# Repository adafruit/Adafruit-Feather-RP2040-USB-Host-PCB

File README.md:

## Adafruit Feather RP2040 with USB Host PCB

<a href="http://www.adafruit.com/products/5723"><br/>
Click here to purchase one from the Adafruit shop</a>

PCB files for the Adafruit Feather RP2040 with USB Host. 

Format is EagleCAD schematic and board layout
* https://www.adafruit.com/product/5723

### Description

You're probably really used to microcontroller boards with USB, but what about a dev board with two? Two is more than one, so that makes it twice as good! And the Adafruit Feather RP2040 with USB Host is definitely double-the-fun of our other Feather RP2040 boards, with a USB Type A port on the end for connecting USB devices to. 

Now you might be thinking "hey waitaminute, the RP2040 doesn't have two USB port peripherals???" and you'd be correct! But what it does have is a nifty PIO peripheral that can be (ab)used to emulate a USB host peripheral. You get to keep the main USB port for uploading, debugging, and data communication, while at the same time sending and receiving data to just-about-any USB device. [This work is originally by sekigon on GitHub](https://github.com/sekigon-gonnoc/Pico-PIO-USB), and if you're using Pico SDK that's still the recommended library to use.

Currently, support for the USB Host peripheral is only in Arduino. So check out the [TinyUSB 'dual role' examples](https://github.com/adafruit/Adafruit_TinyUSB_Arduino/tree/master/examples/DualRole) for some things you can do! For example, [datalogging to a USB Key](https://github.com/adafruit/Adafruit_TinyUSB_Arduino/tree/master/examples/DualRole/MassStorage/msc_data_logger). Or [reading from another device/microcontroller that has USB CDC serial interface](https://github.com/adafruit/Adafruit_TinyUSB_Arduino/tree/master/examples/DualRole/CDC/serial_host_bridge). Or [creating an HID re-mapper](https://github.com/adafruit/Adafruit_TinyUSB_Arduino/tree/master/examples/DualRole/HID/hid_remapper). Or [connecting to weird devices that require firmware-updates like the Cypress EZ-USB based Intellikeys](https://github.com/adafruit/Adafruit_IntelliKeys) communications board.

Note that this is definitely a firmware hack: you will need to dedicate the second ARM core and both PIO peripherals to just handling the USB messages, but we find that it does work fairly well, or at least as well as most microcontroller's USB Host peripherals!

We also include a 1 Amp boost converter based on the TPS61023 so you can run from Lipo battery and get a nice clean 5V output for the USB devices. The booster has the enable pin tied to one of the extra GPIO on the RP2040 so power can be manually turned on and off to hard-reset whatever is connected.

At the Feather's heart is an RP2040 chip, clocked at 133 MHz and at 3.3V logic, the same one used in the Raspberry Pi Pico. This chip has a whopping 8MB of onboard QSPI FLASH and 264K of RAM!  There's even room left over for a STEMMA QT connector for plug-and-play of I2C devices!

To make it easy to use for portable projects, we added a connector for any of our 3.7V Lithium polymer batteries and built-in battery charging. You don't need a battery, it will run just fine straight from the USB Type C connector. But, if you do have a battery, you can take it on the go, then plug in the USB to recharge. The Feather will automatically switch over to USB power when it's available.

Here're some handy specs! You get:

* Measures 2.0" x 0.9" x 0.28" (50.8mm x 22.8mm x 7mm) without headers soldered in
* Light as a (large?) feather - 6.3 grams
* RP2040 32-bit Cortex M0+ dual core running at ~133 MHz @ 3.3V logic and power
* 264 KB RAM
* 8 MB SPI FLASH chip for storing files and CircuitPython/MicroPython code storage. No EEPROM
* Tons of GPIO! 21 x GPIO pins with following capabilities:
* Four 12-bit ADCs (one more than Pico)
* Two I2C, Two SPI, and two UART peripherals, we label one for the 'main' interface in standard Feather locations
* 16 x PWM outputs - for servos, LEDs, etc
* Built-in 200mA+ lipoly charger with charging status indicator LED
* Pin #13 red LED for general purpose blinking
* RGB NeoPixel for full-color indication.
* On-board STEMMA QT connector that lets you quickly connect any Qwiic, STEMMA QT or Grove I2C devices with no soldering!
* Both Reset button and Bootloader select button for quick restarts (no unplugging-replugging to relaunch code)
* USB Type C connector lets you access built-in ROM USB bootloader and serial port debugging
* USB Type A connector for USB host capability. D+ on GPIO 16, D- on GPIO 17
* 5V Boost converter, up to 1 Amp peak output for USB peripheral power, with 500mA resettable fuse. Enable on GPIO 18. 
* 3.3V Power/enable pin
* 4 mounting holes
* 12 MHz crystal for perfect timing.
* 3.3V regulator with 500mA peak current output

### License

Adafruit invests time and resources providing this open source design, please support Adafruit and open-source hardware by purchasing products from [Adafruit](https://www.adafruit.com)!

Designed by Limor Fried/Ladyada for Adafruit Industries.

Creative Commons Attribution/Share-Alike, all text above must be included in any redistribution. 
See license.txt for additional details.

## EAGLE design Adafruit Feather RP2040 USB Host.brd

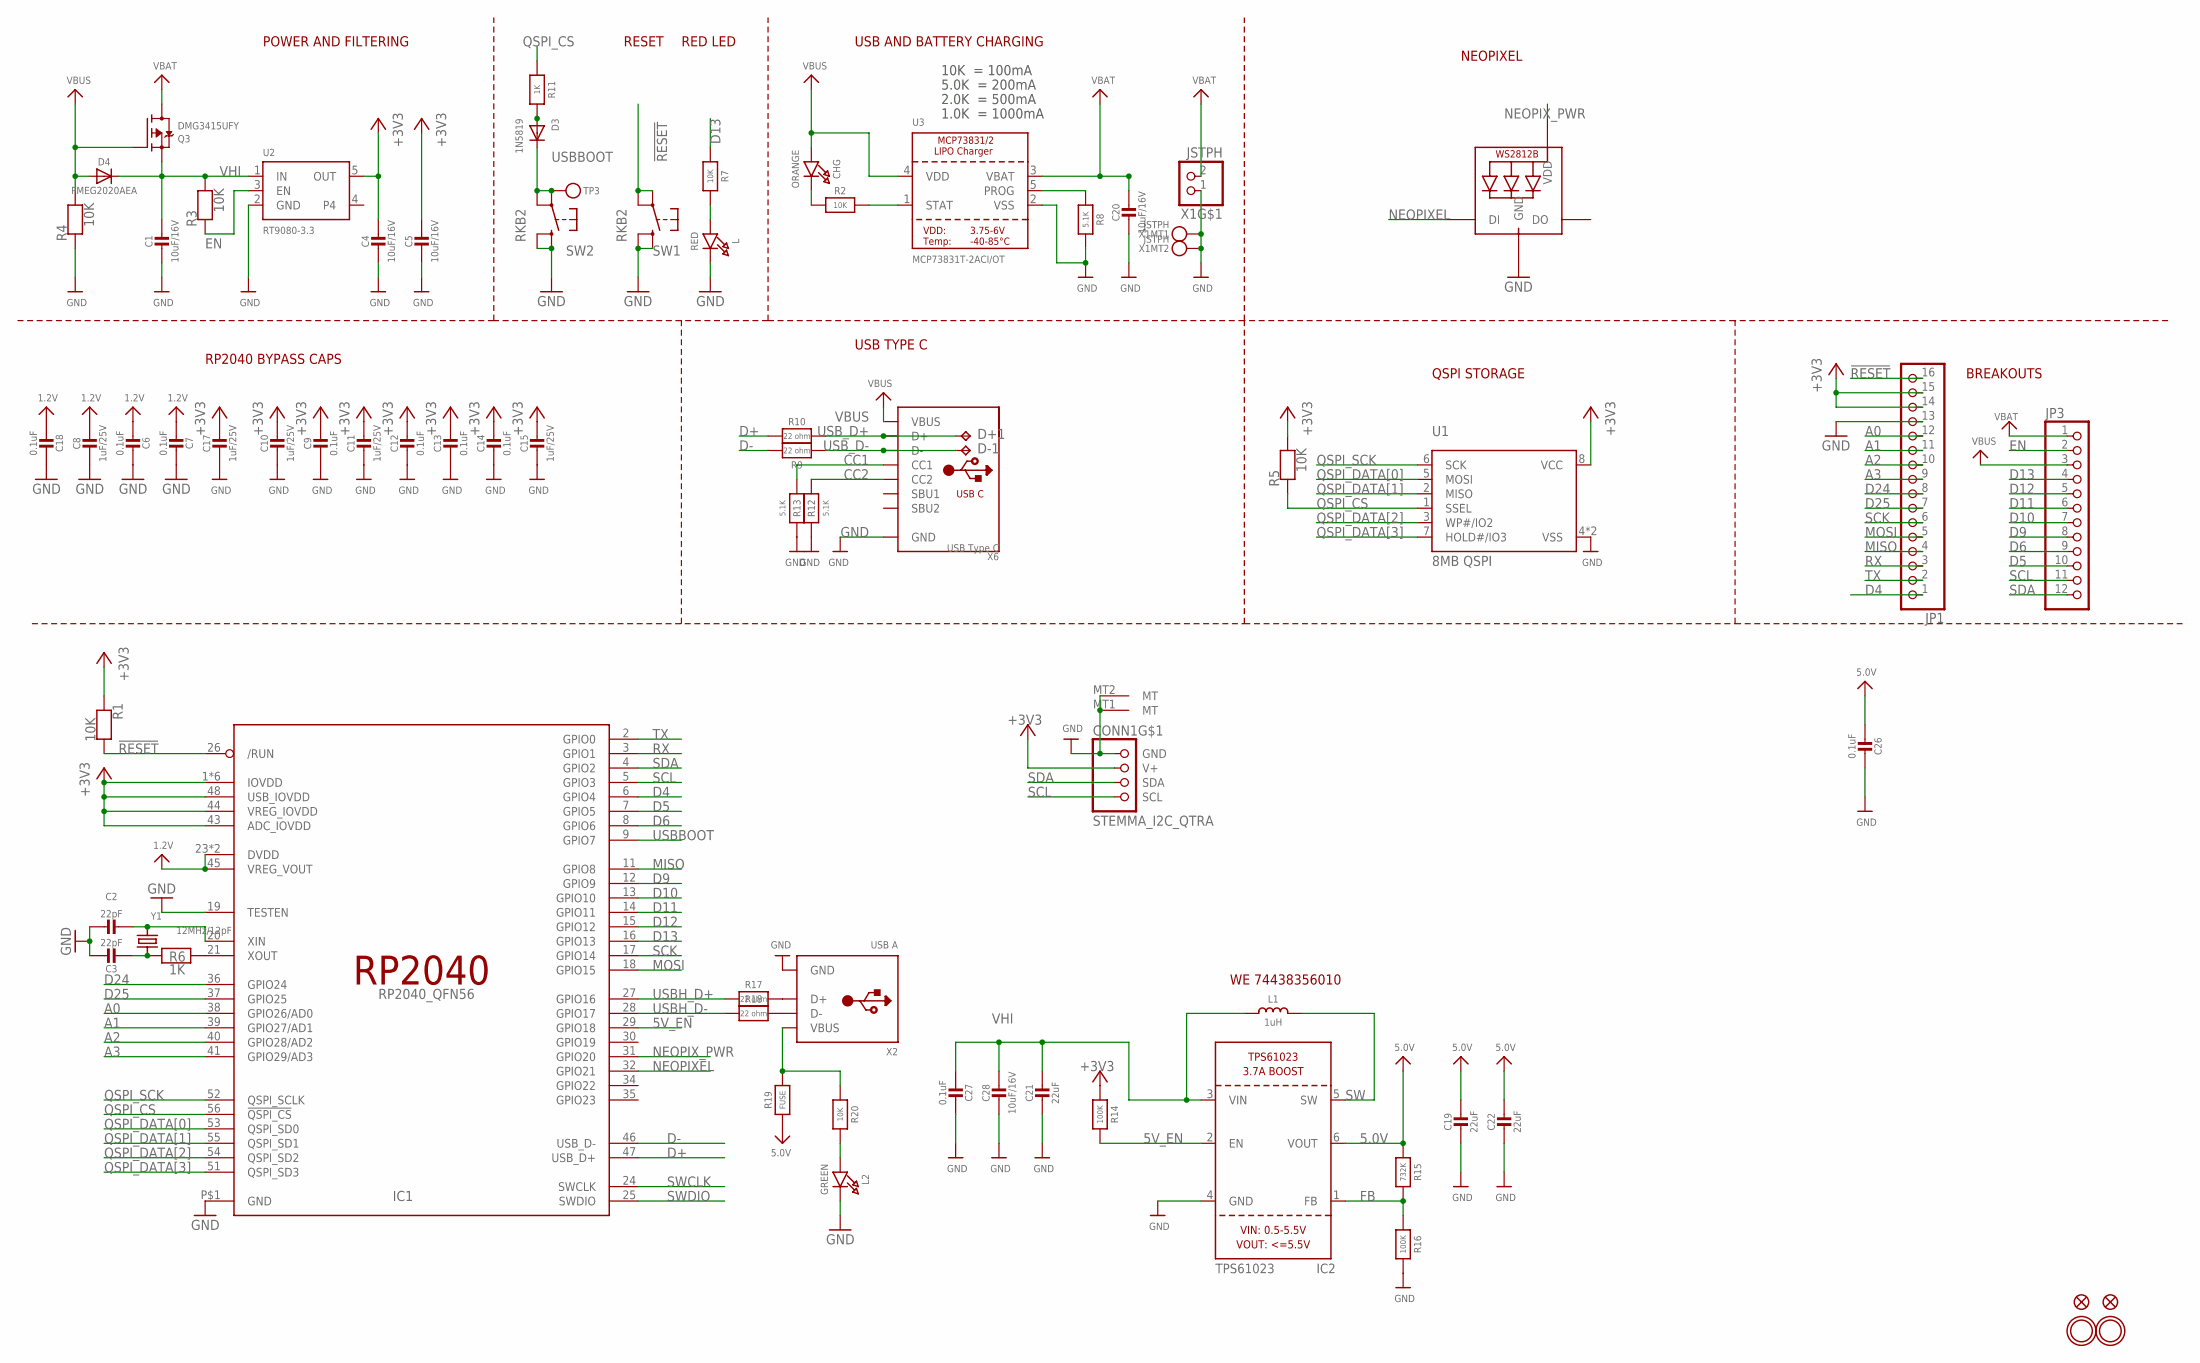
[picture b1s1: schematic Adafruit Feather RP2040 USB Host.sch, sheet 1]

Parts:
C1, C4, C5, C20, C28: 10uF/16V; 0805-NO
C2, C3: 22pF; _0402NO
C6, C7, C9, C12, C13, C14, C18, C26, C27: 0.1uF; _0402NO
C8, C10, C11, C15, C17: 1uF/25V; _0402NO
C19, C21, C22: 22uF; 0805-NO
CHG: ORANGE; CHIPLED_0603_NOOUTLINE
CONN1: STEMMA_I2C_QTRA; JST_SH4_RA
D3: 1N5819; SOD-323_MINI
D4: PMEG2020AEA; SOD-323F
D+1: TPB1,27; B1,27
D-1: TPB1,27; B1,27
IC1: RP2040_QFN56; QFN56_7MM_REDUCEDEPAD
IC2: TPS61023; SOT563
JP1: HEADER-1X16ROUND; 1X16_ROUND
JP3: HEADER-1X12; 1X12_ROUND
L: RED; CHIPLED_0603_NOOUTLINE
L1: 1uH; INDUCTOR_5045_SMALLTABS
L2: GREEN; CHIPLED_0603_NOOUTLINE
LED1: WS2812B_SK6805_1515; SK6805_1515
Q3: DMG3415UFY; DFN2015-3
R1, R2, R3, R4, R5, R7, R20: 10K; _0402NO
R6, R11: 1K; _0402NO
R8, R12, R13: 5.1K; _0402NO
R9, R10, R17, R18: 22 ohm; _0402NO
R14, R16: 100K; _0402NO
R15: 732K; _0402NO
R19: FUSE; 0805-NO
SW1, SW2: RKB2; BTN_RKB2_4.6X2.8
TP3: TESTPOINTROUND1.5MMNO; TESTPOINT_ROUND_1.5MM_NO
U1: 8MB QSPI; USON8_4X4
U2: RT9080-3.3; SOT23-5; JLC_ROTATION 0
U3: MCP73831T-2ACI/OT; SOT23-5
U$31, U$32: MOUNTINGHOLE2.5; MOUNTINGHOLE_2.5_PLATED
U$34, U$35: FIDUCIAL_1MM
X1: JSTPH; JSTPH2_BATT
X2: USB A; USB_HOST-SMT
X6: USB Type C; USB_C_CUSB31-CFM2AX-01-X
Y1: 12MHz/12pF; CRYSTAL_2.5X2

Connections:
1.2V: C6.2, C7.2, C8.1, C18.2, IC1.23 (DVDD), IC1.45 (VREG_VOUT), IC1.50 (DVDD)
5.0V: C19.1, C22.1, C26.2, IC2.6 (VOUT), R15.1, R19.2
5V_EN: IC1.29 (GPIO18), IC2.2 (EN), R14.2
!RESET: IC1.26 (/RUN), JP1.16, R1.2, SW1.A, SW1.A' (P1)
+3V3: C4.1, C5.1, C9.1, C10.1, C11.1, C12.1, C13.1, C14.1, C15.1, C17.1, CONN1.2 (V+), IC1.1 (IOVDD), IC1.10 (IOVDD), IC1.22 (IOVDD), IC1.33 (IOVDD), IC1.42 (IOVDD), IC1.43 (ADC_IOVDD), IC1.44 (VREG_IOVDD), IC1.48 (USB_IOVDD), IC1.49 (IOVDD), JP1.14, JP1.15, R1.1, R5.2, R14.1, U1.8 (VCC), U2.5 (OUT)
A0: IC1.38 (GPIO26/AD0), JP1.12
A1: IC1.39 (GPIO27/AD1), JP1.11
A2: IC1.40 (GPIO28/AD2), JP1.10
A3: IC1.41 (GPIO29/AD3), JP1.9
CC1: R13.2, X6.A5 (CC1)
CC2: R12.2, X6.B5 (CC2)
D4: IC1.6 (GPIO4), JP1.1
D5: IC1.7 (GPIO5), JP3.10
D6: IC1.8 (GPIO6), JP3.9
D9: IC1.12 (GPIO9), JP3.8
D10: IC1.13 (GPIO10), JP3.7
D11: IC1.14 (GPIO11), JP3.6
D12: IC1.15 (GPIO12), JP3.5
D13: IC1.16 (GPIO13), JP3.4, R7.1
D24: IC1.36 (GPIO24), JP1.8
D25: IC1.37 (GPIO25), JP1.7
D+: IC1.47 (USB_D+), R10.2
D-: IC1.46 (USB_D-), R9.2
EN: JP3.2, R3.1, U2.3 (EN)
FB: IC2.1 (FB), R15.2, R16.1
GND: C1.2, C2.1, C3.1, C4.2, C5.2, C6.1, C7.1, C8.2, C9.2, C10.2, C11.2, C12.2, C13.2, C14.2, C15.2, C17.2, C18.1, C19.2, C20.2, C21.2, C22.2, C26.1, C27.1, C28.2, CONN1.1 (GND), CONN1.MT1 (MT), CONN1.MT2 (MT), IC1.19 (TESTEN), IC1.P$1 (GND), IC2.4 (GND), JP1.13, L.C, L2.C, LED1.4 (GND), R4.1, R8.2, R12.1, R13.1, R16.2, SW1.B (S), SW1.B' (S1), SW2.B (S), SW2.B' (S1), U1.4 (VSS), U1.PAD (VSS), U2.2 (GND), U3.2 (VSS), X1.1, X1.NC1, X1.NC2, X2.GND, X6.A1B12 (GND), X6.B1A12 (GND)
MISO: IC1.11 (GPIO8), JP1.4
MOSI: IC1.18 (GPIO15), JP1.5
unnamed: CHG.C, R2.1
unnamed: L.A, R7.2
unnamed: R2.2, U3.1 (STAT)
unnamed: R8.1, U3.5 (PROG)
unnamed: C2.2, IC1.20 (XIN), Y1.3 (2)
unnamed: C3.2, R6.1, Y1.1
unnamed: IC1.21 (XOUT), R6.2
unnamed: R17.1, X2.D+
unnamed: R18.1, X2.D-
unnamed: R19.1, R20.1, X2.VBUS
unnamed: L2.A, R20.2
unnamed: D3.A, R11.2
NEOPIXEL: IC1.32 (GPIO21), LED1.1 (DI)
NEOPIX_PWR: IC1.31 (GPIO20), LED1.2 (VDD)
QSPI_CS: IC1.56 (!QSPI_CS), R5.1, R11.1, U1.1 (SSEL)
QSPI_DATA[0]: IC1.53 (QSPI_SD0), U1.5 (MOSI)
QSPI_DATA[1]: IC1.55 (QSPI_SD1), U1.2 (MISO)
QSPI_DATA[2]: IC1.54 (QSPI_SD2), U1.3 (WP#/IO2)
QSPI_DATA[3]: IC1.51 (QSPI_SD3), U1.7 (HOLD#/IO3)
QSPI_SCK: IC1.52 (QSPI_SCLK), U1.6 (SCK)
RX: IC1.3 (GPIO1), JP1.3
SCK: IC1.17 (GPIO14), JP1.6
SCL: CONN1.4 (SCL), IC1.5 (GPIO3), JP3.11
SDA: CONN1.3 (SDA), IC1.4 (GPIO2), JP3.12
SW: IC2.5 (SW), L1.2
SWCLK: IC1.24 (SWCLK)
SWDIO: IC1.25 (SWDIO)
TX: IC1.2 (GPIO0), JP1.2
USBBOOT: D3.C, IC1.9 (GPIO7), SW2.A, SW2.A' (P1), TP3.P$1
USBH_D+: IC1.27 (GPIO16), R17.2
USBH_D-: IC1.28 (GPIO17), R18.2
USB_D+: D+1.TP, R10.1, X6.A6 (D+), X6.B6 (D+)
USB_D-: D-1.TP, R9.1, X6.A7 (D-), X6.B7 (D-)
VBAT: C20.1, JP3.1, Q3.3 (D), U3.3 (VBAT), X1.2
VBUS: CHG.A, D4.A, JP3.3, Q3.1 (G), R4.2, U3.4 (VDD), X6.A4B9 (VBUS), X6.B4A9 (VBUS)
VHI: C1.1, C21.1, C27.2, C28.1, D4.C, IC2.3 (VIN), L1.1, Q3.2 (S), R3.2, U2.1 (IN)

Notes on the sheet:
POWER AND FILTERING
RESET
10K = 100mA
5.0K = 200mA
2.0K = 500mA
1.0K = 1000mA
USB AND BATTERY CHARGING
BREAKOUTS
RED LED
RP2040 BYPASS CAPS
USB TYPE C
QSPI STORAGE
NEOPIXEL
WE 74438356010

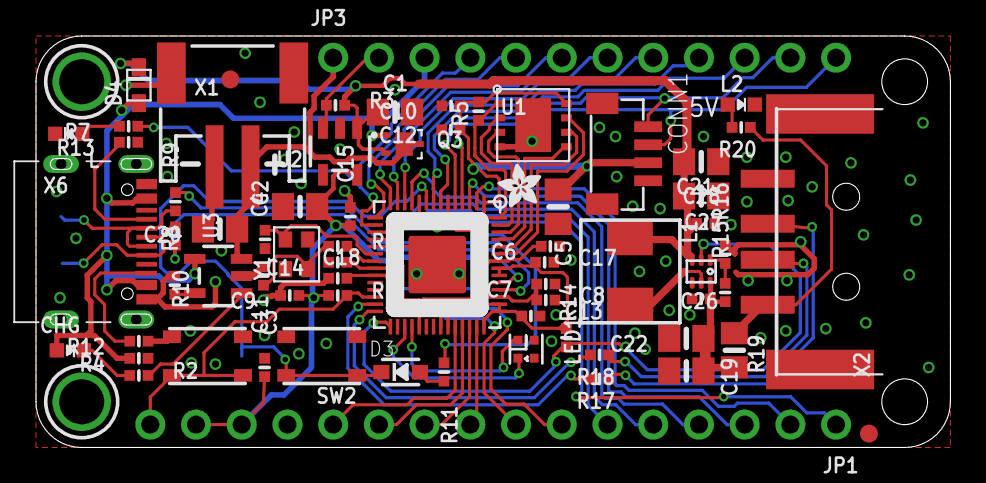
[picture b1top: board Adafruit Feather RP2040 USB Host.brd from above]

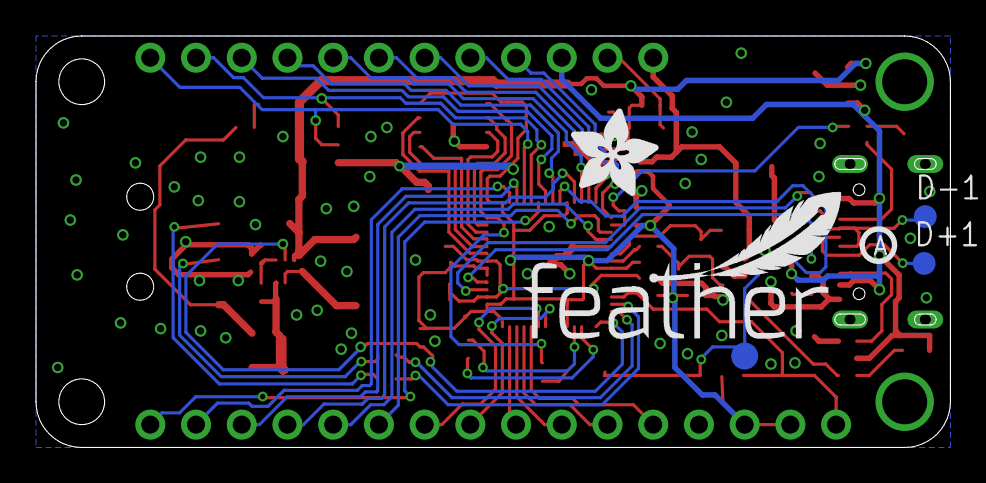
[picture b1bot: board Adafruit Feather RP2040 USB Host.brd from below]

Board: 2 copper layers, 50.8 x 22.9 mm, 140 parts (37 on the bottom side), 62 nets.

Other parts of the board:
PLABEL0: PLABEL0
PLABEL1: PLABEL1
PLABEL2: PLABEL2
PLABEL3: PLABEL3
PLABEL4: PLABEL4
PLABEL5: PLABEL5
PLABEL6: PLABEL6
PLABEL7: PLABEL7
PLABEL8: PLABEL8
PLABEL9: PLABEL9
PLABEL10: PLABEL10
PLABEL11: PLABEL11
PLABEL12: PLABEL12
PLABEL13: PLABEL13
PLABEL14: PLABEL14
PLABEL15: PLABEL15
PLABEL16: PLABEL16
PLABEL17: PLABEL17
PLABEL18: PLABEL18
PLABEL19: PLABEL19
PLABEL20: PLABEL20
PLABEL21: PLABEL21
PLABEL22: PLABEL22
PLABEL23: PLABEL23
PLABEL24: PLABEL24
PLABEL25: PLABEL25
PLABEL26: PLABEL26
PLABEL27: PLABEL27
PLABEL28: PLABEL28
PLABEL29: PLABEL29
PLABEL30: PLABEL30
PLABEL31: PLABEL31
PLABEL32: PLABEL32
PLABEL33: PLABEL33
PLABEL34: PLABEL34
PLABEL35: PLABEL35
PLABEL36: PLABEL36
PLABEL37: PLABEL37
PLABEL38: PLABEL38
PLABEL39: PLABEL39
PLABEL40: PLABEL40
PLABEL41: PLABEL41
PLABEL42: PLABEL42
PLABEL43: PLABEL43
PLABEL44: PLABEL44
PLABEL45: PLABEL45
PLABEL46: PLABEL46
PLABEL47: PLABEL47
PLABEL48: PLABEL48
PLABEL49: PLABEL49
PLABEL50: PLABEL50
PLABEL51: PLABEL51
PLABEL52: PLABEL52
PLABEL53: PLABEL53
PLABEL54: PLABEL54
PLABEL55: PLABEL55
PLABEL56: PLABEL56
PLABEL57: PLABEL57
PLABEL58: PLABEL58
PLABEL59: PLABEL59
PLABEL60: PLABEL60
PLABEL61: PLABEL61
PLABEL62: PLABEL62
U$13: PCBFEAT-REV-040
U$43: ADAFRUIT_2.5MM
U$46: FEATHERLOGO_MED
U$47: ADAFRUIT_5MM

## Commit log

2023-04-24 adding cookiecutter output
2023-04-24 adding links to readme
2023-04-24 adding prettypins
2023-04-24 adding factory reset
2023-08-29 updating factory reset uf2
2025-09-24 Change battery connector to correct view

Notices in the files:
parts and their libraries:
microbuilder: This work is placed in the public domain, and may be freely used for commercial and non-commercial work with the following conditions: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
